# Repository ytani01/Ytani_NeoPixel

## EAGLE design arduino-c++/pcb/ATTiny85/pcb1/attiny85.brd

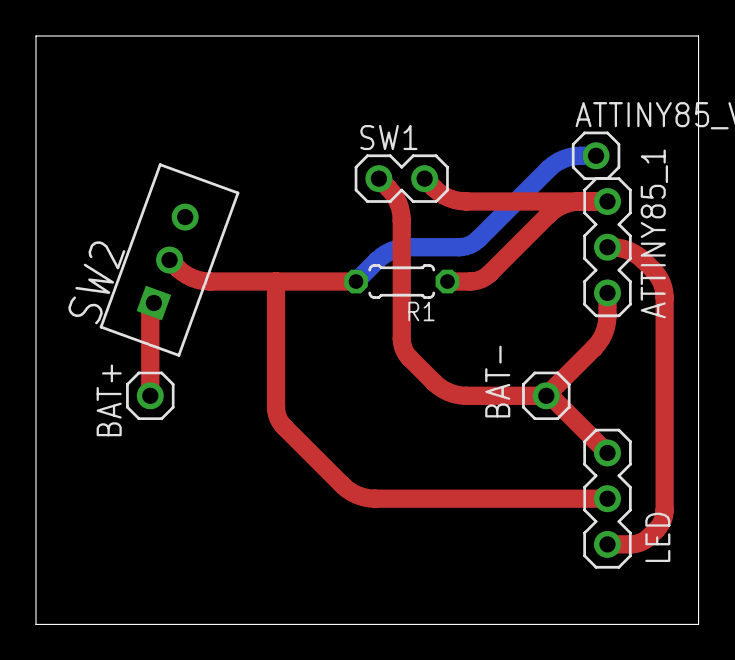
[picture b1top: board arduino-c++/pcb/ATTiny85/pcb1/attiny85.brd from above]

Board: 2 copper layers, 36.8 x 32.7 mm, 8 parts (0 on the bottom side), 5 nets.

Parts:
ATTINY85_1: PINHEAD-MA03-1
ATTINY85_VCC: PINHEAD-MA01-1
BAT+: PINHEAD-MA01-1
BAT-: PINHEAD-MA01-1
LED: PINHEAD-MA03-1
R1: 0204/5
SW1: PINHEAD-MA02-1
SW2: SW3-1

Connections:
+3V3: BAT+.1, SW2.1
BAT+: ATTINY85_VCC.1, LED.2, R1.2, SW2.2
GND: ATTINY85_1.1, BAT-.1, LED.1, SW1.1
PB3: ATTINY85_1.3, R1.1, SW1.2
PB4: ATTINY85_1.2, LED.3

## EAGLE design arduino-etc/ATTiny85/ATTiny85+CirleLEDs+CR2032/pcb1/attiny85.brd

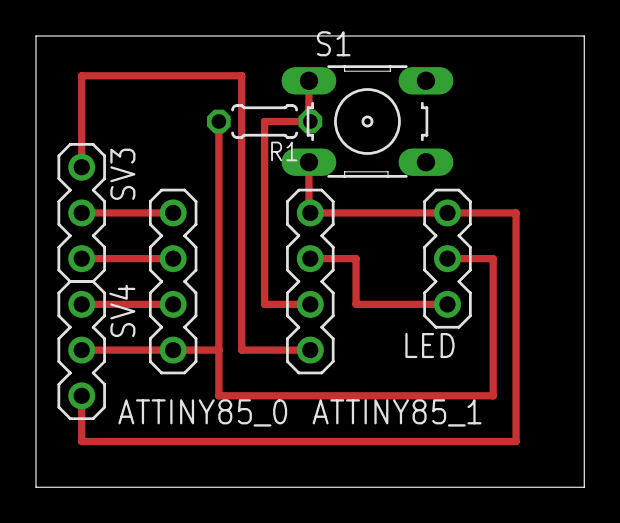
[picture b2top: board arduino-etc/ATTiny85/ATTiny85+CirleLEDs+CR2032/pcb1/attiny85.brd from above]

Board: 2 copper layers, 30.5 x 25.1 mm, 7 parts (0 on the bottom side), 8 nets.

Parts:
ATTINY85_0, ATTINY85_1: PINHEAD-MA04-1
LED: PINHEAD-MA03-1
R1: 0204/5
S1: B3F-10XX
SV3, SV4: PINHEAD-MA03-1

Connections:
BAT+: ATTINY85_0.4, LED.2, R1.2, SV4.2
GND: ATTINY85_1.1, LED.1, S1.3, SV4.3
unnamed: ATTINY85_0.3, SV4.1
unnamed: ATTINY85_1.4, SV3.1
unnamed: ATTINY85_0.2, SV3.3
unnamed: ATTINY85_0.1, SV3.2
PB3: ATTINY85_1.3, R1.1, S1.1
PB4: ATTINY85_1.2, LED.3

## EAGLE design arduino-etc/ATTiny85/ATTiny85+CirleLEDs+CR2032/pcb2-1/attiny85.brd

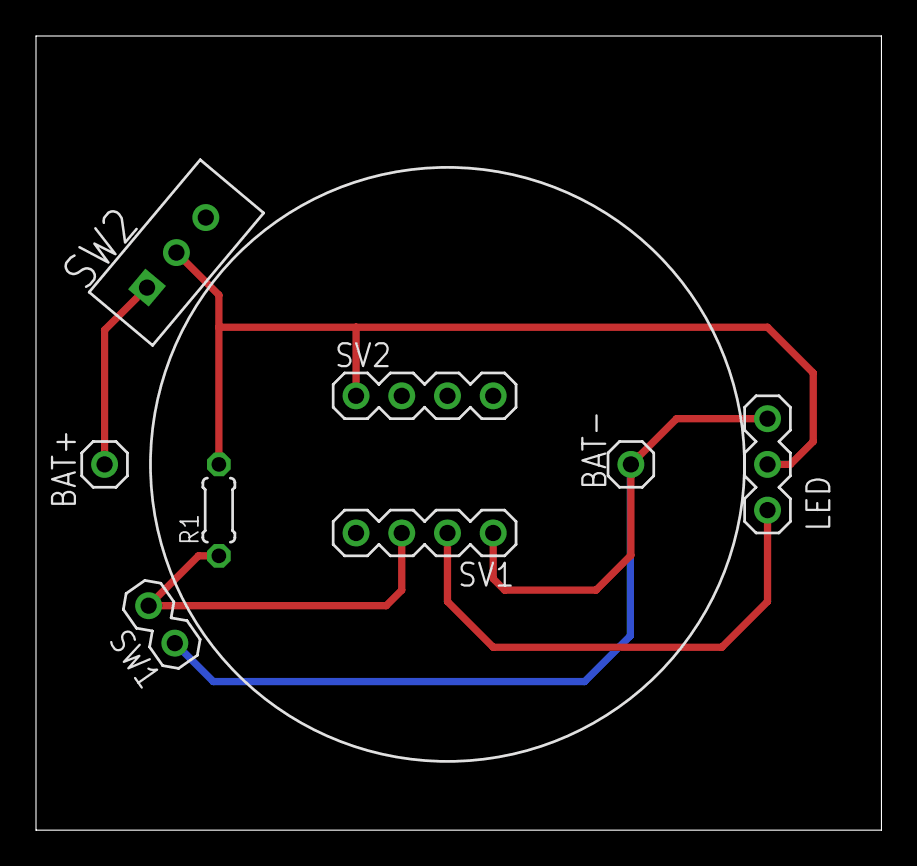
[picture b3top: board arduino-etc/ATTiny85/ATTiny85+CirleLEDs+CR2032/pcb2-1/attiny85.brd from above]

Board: 2 copper layers, 47.0 x 44.1 mm, 8 parts (0 on the bottom side), 5 nets.

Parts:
BAT+: PINHEAD-MA01-1
BAT-: PINHEAD-MA01-1
LED: PINHEAD-MA03-1
R1: 0204/5
SV1, SV2: PINHEAD-MA04-1
SW1: PINHEAD-MA02-1
SW2: SW3-1

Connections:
+3V3: BAT+.1, SW2.1
BAT+: LED.2, R1.2, SV2.1, SW2.2
GND: BAT-.1, LED.1, SV1.1, SW1.1
PB3: R1.1, SV1.3, SW1.2
PB4: LED.3, SV1.2

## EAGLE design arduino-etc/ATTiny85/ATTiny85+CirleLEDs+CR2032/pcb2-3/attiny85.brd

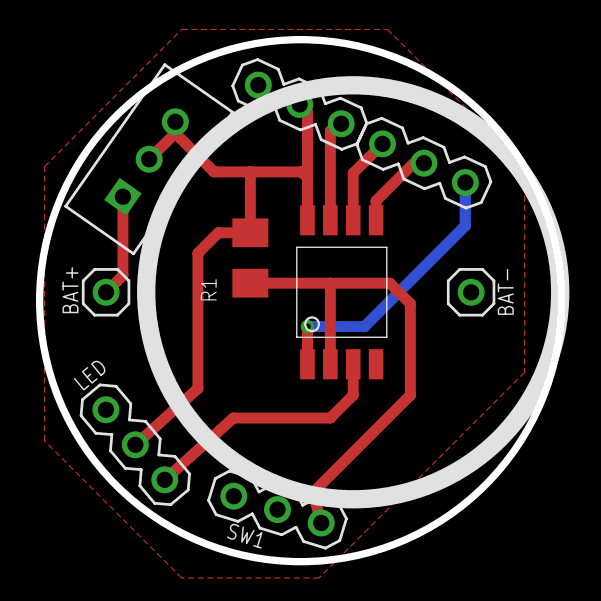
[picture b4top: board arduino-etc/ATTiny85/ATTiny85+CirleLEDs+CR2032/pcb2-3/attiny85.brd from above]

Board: 2 copper layers, 29.0 x 29.0 mm, 10 parts (1 on the bottom side), 9 nets.

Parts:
ATTINY85-1: ATTINY85; ATTINY85-20SUR
BAT+: bat+; PINHEAD-MA01-1
BAT-: bat-; PINHEAD-MA01-1
LED: LED1; PINHEAD-MA03-1
LOGO1: LOGO-YT1
R1: 10K; M3216
SV1: PIN-A; PINHEAD-MA03-1
SV2: PIN-B; PINHEAD-MA03-1
SW1: bat+; PINHEAD-MA03-1
SW2: POWER; SW3-1

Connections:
+3V3: BAT+.1, SW2.1
BAT+: ATTINY85-1.P8, LED.2, R1.2, SV2.2, SW2.2, SW2.3
GND: ATTINY85-1.P4, BAT-.1, LED.1, SV2.3, SW1.1, SW1.2
unnamed: ATTINY85-1.P3, LED.3
unnamed: ATTINY85-1.P7, SV2.1
unnamed: ATTINY85-1.P6, SV1.3
unnamed: ATTINY85-1.P1, SV1.1
unnamed: ATTINY85-1.P5, SV1.2
PB3: ATTINY85-1.P2, R1.1, SW1.3

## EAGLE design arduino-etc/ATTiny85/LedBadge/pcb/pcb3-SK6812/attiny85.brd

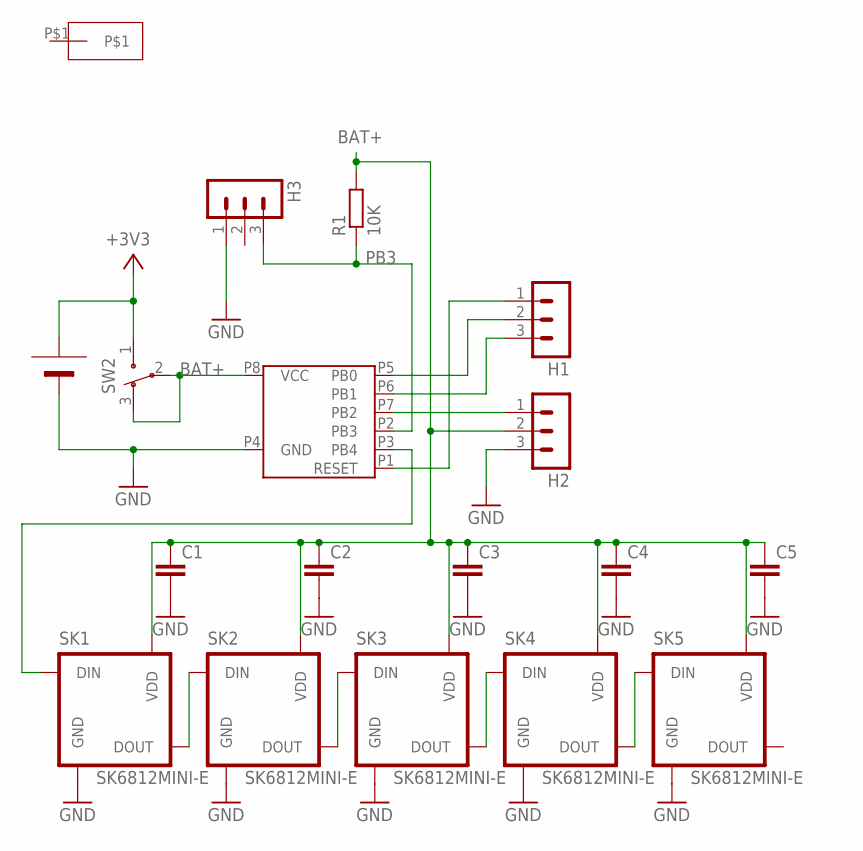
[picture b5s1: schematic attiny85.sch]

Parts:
ATTINY85-1: ATTINY85; ATTINY85-20SUR
BAT1: BAT-CR2032; BAT-CR2032-1
C1, C2, C3, C4, C5: C-EUC2012; C2012
H1, H2: PINHEAD-MA03-1SMD; PINHEAD-MA03-2
H3: PINHEAD-MA03-1
PAD33: PAD12X4; PAD-12X4
R1: 10K; M3216
SK1, SK2, SK3, SK4, SK5: SK6812MINI-E
SW2: POWER; SW3-1

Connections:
+3V3: BAT1.BAT+, SW2.1
BAT+: ATTINY85-1.P8 (VCC), C1.1, C2.1, C3.1, C4.1, C5.1, H2.2, R1.2, SK1.VDD, SK2.VDD, SK3.VDD, SK4.VDD, SK5.VDD, SW2.2, SW2.3
GND: ATTINY85-1.P4 (GND), BAT1.BAT-, C1.2, C2.2, C3.2, C4.2, C5.2, H2.3, H3.1, SK1.GND, SK2.GND, SK3.GND, SK4.GND, SK5.GND
unnamed: ATTINY85-1.P3 (PB4), SK1.DIN
unnamed: ATTINY85-1.P7 (PB2), H2.1
unnamed: ATTINY85-1.P6 (PB1), H1.3
unnamed: ATTINY85-1.P1 (RESET), H1.1
unnamed: ATTINY85-1.P5 (PB0), H1.2
unnamed: SK1.DOUT, SK2.DIN
unnamed: SK2.DOUT, SK3.DIN
unnamed: SK3.DOUT, SK4.DIN
unnamed: SK4.DOUT, SK5.DIN
PB3: ATTINY85-1.P2 (PB3), H3.3, R1.1

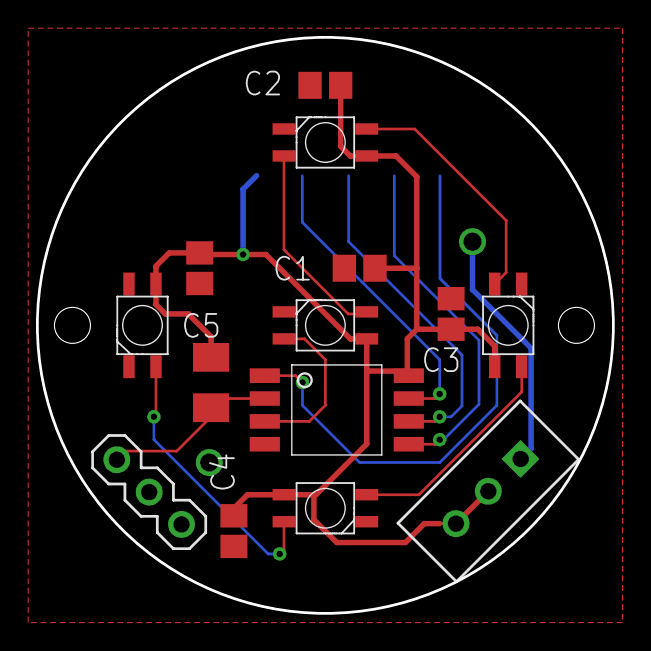
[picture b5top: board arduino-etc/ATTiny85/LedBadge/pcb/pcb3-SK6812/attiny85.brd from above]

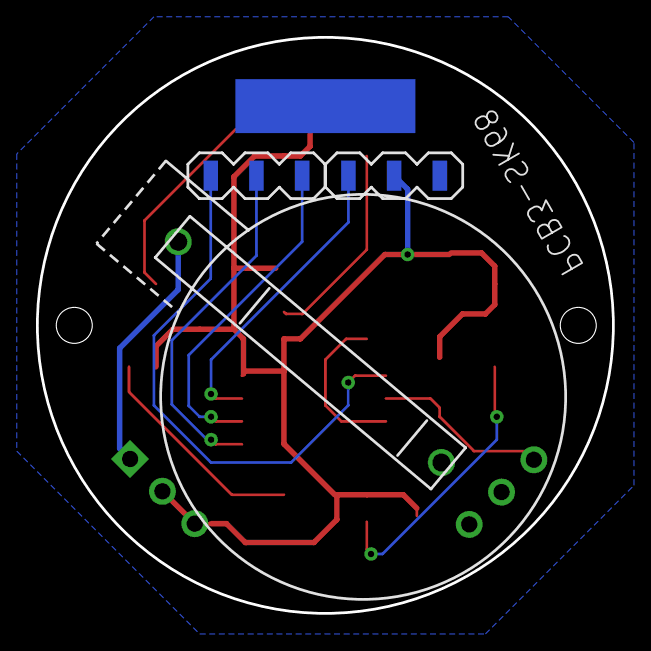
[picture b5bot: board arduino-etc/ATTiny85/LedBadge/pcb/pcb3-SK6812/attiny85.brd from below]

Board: 2 copper layers, 32.0 x 32.0 mm, 18 parts (4 on the bottom side), 13 nets.
